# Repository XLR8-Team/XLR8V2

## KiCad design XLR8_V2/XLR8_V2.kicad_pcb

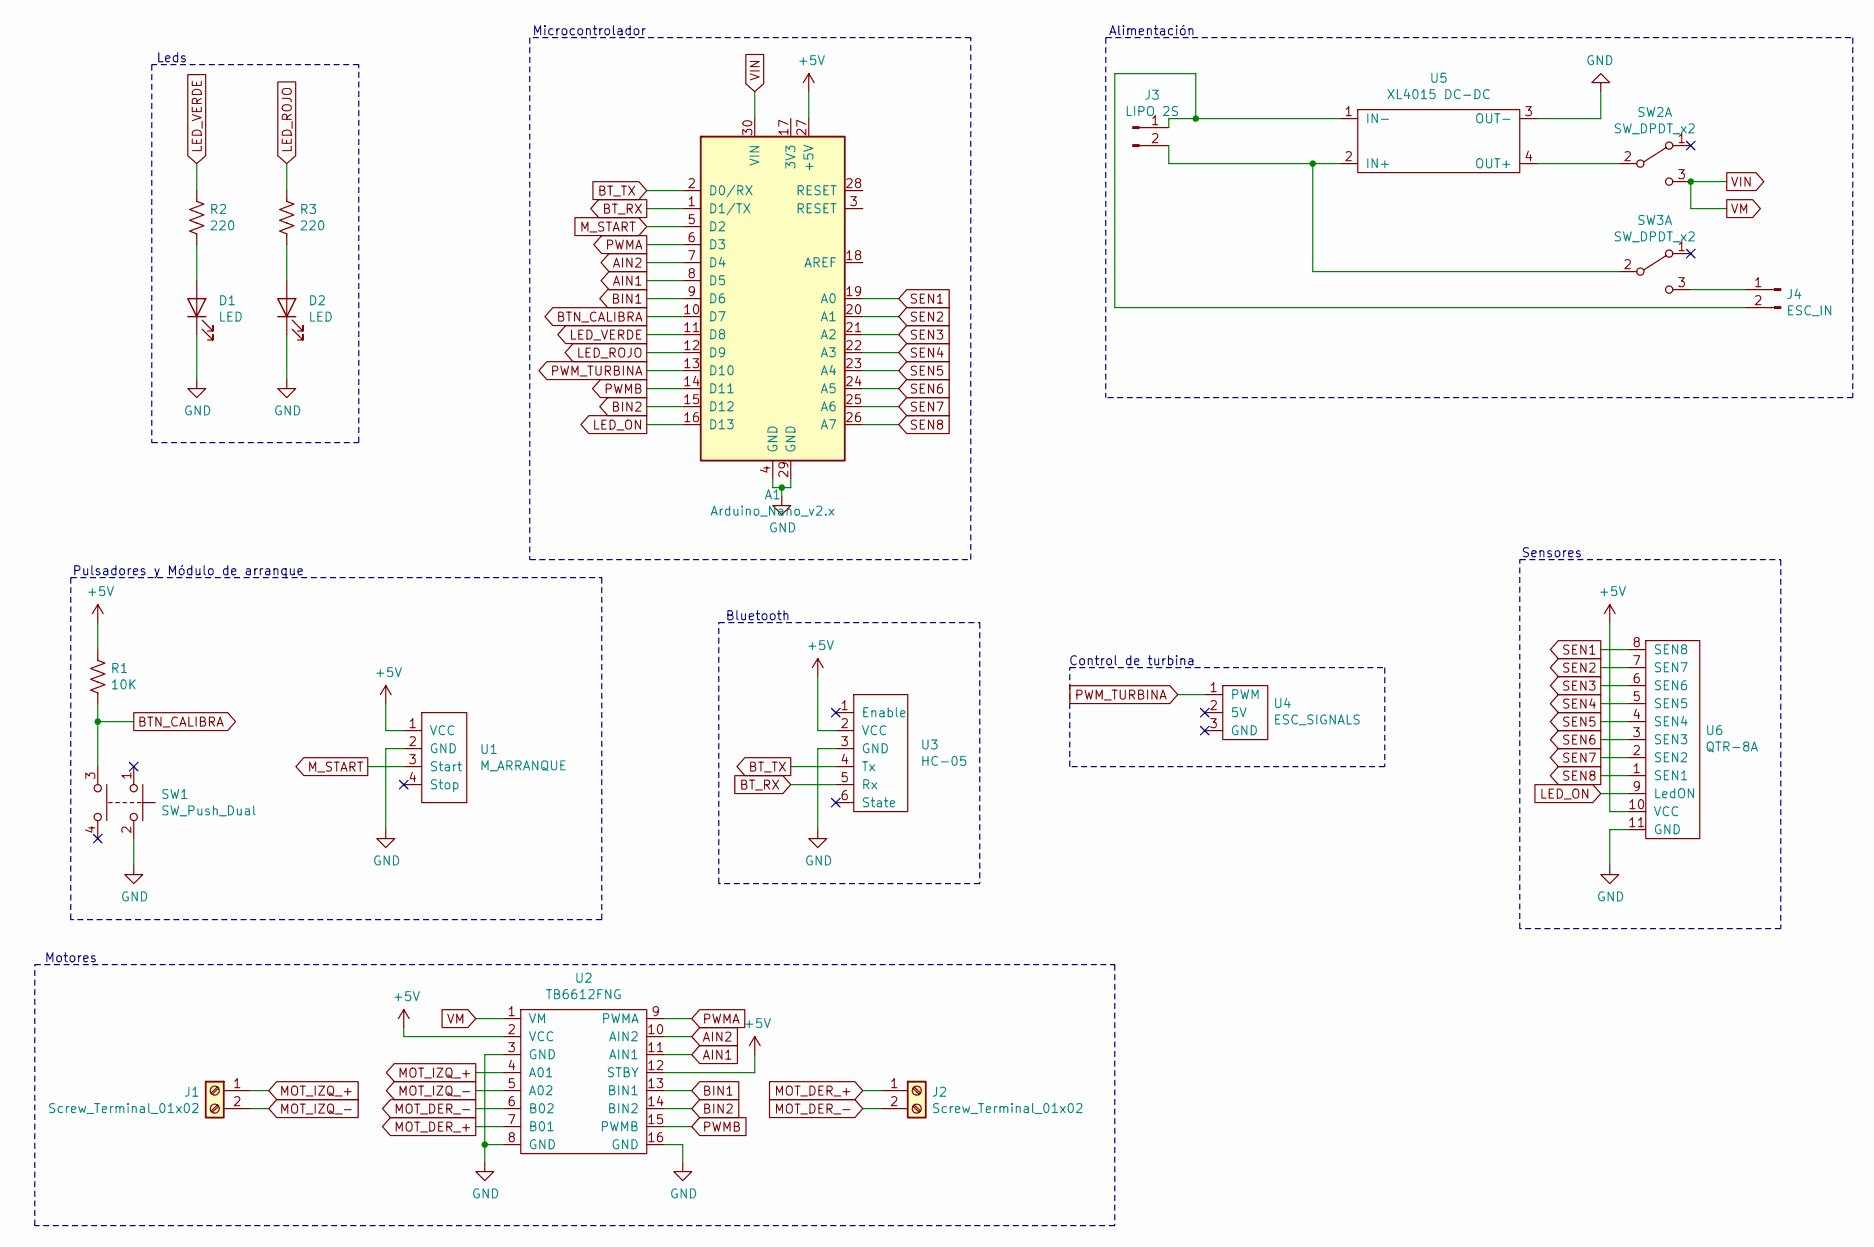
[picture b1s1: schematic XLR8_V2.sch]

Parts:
A1: Arduino_Nano_v2.x; Arduino_Nano_WithMountingHoles
D1, D2: LED; LED_D3.0mm
J1, J2: Screw_Terminal_01x02; TerminalBlock_bornier-2_P5.08mm
J3: LIPO 2S; AMASS_XT30U-M_1x02_P5.0mm_Vertical
J4: ESC_IN; PinHeader_1x02_P2.54mm_Vertical
R1: 10K; R_Axial_DIN0207_L6.3mm_D2.5mm_P7.62mm_Horizontal
R2, R3: 220; R_Axial_DIN0207_L6.3mm_D2.5mm_P7.62mm_Horizontal
SW1: SW_Push_Dual; SW_PUSH_6mm
SW2, SW3: SW_DPDT_x2; SW_CuK_OS102011MA1QN1_SPDT_Angled
U1: M_ARRANQUE; PinSocket_1x04_P2.54mm_Vertical
U2: TB6612FNG
U3: HC-05; PinSocket_1x06_P2.54mm_Vertical
U4: ESC_SIGNALS; PinHeader_1x03_P2.54mm_Vertical
U5: XL4015 DC-DC; XL4015_Converter
U6: QTR-8A; PinHeader_1x11_P2.54mm_Vertical

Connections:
+5V: A1.27 (+5V), R1.1, U1.1 (VCC), U2.2 (VCC), U2.12 (STBY), U3.2 (VCC), U6.10 (VCC)
AIN1: A1.8 (D5), U2.11 (AIN1)
AIN2: A1.7 (D4), U2.10 (AIN2)
BIN1: A1.9 (D6), U2.13 (BIN1)
BIN2: A1.15 (D12), U2.14 (BIN2)
BTN_CALIBRA: A1.10 (D7), R1.2, SW1.3
BT_RX: A1.1 (D1/TX), U3.5 (Rx)
BT_TX: A1.2 (D0/RX), U3.4 (Tx)
GND: A1.4 (GND), A1.29 (GND), D1.1 (K), D2.1 (K), SW1.2, U1.2 (GND), U2.3 (GND), U2.8 (GND), U2.16 (GND), U3.3 (GND), U5.3 (OUT-), U6.11 (GND)
LED_ON: A1.16 (D13), U6.9 (LedON)
LED_ROJO: A1.12 (D9), R3.1
LED_VERDE: A1.11 (D8), R2.1
MOT_DER_+: J2.1, U2.7 (B01)
MOT_DER_-: J2.2, U2.6 (B02)
MOT_IZQ_+: J1.1, U2.4 (A01)
MOT_IZQ_-: J1.2, U2.5 (A02)
M_START: A1.5 (D2), U1.3 (Start)
unnamed: D1.2 (A), R2.2
unnamed: D2.2 (A), R3.2
unnamed: J3.1, J4.2, U5.1 (IN-)
unnamed: J3.2, SW3.2 (B), U5.2 (IN+)
unnamed: J4.1, SW3.3 (C)
unnamed: SW2.2 (B), U5.4 (OUT+)
PWMA: A1.6 (D3), U2.9 (PWMA)
PWMB: A1.14 (D11), U2.15 (PWMB)
PWM_TURBINA: A1.13 (D10), U4.1 (PWM)
SEN1: A1.19 (A0), U6.8 (SEN8)
SEN2: A1.20 (A1), U6.7 (SEN7)
SEN3: A1.21 (A2), U6.6 (SEN6)
SEN4: A1.22 (A3), U6.5 (SEN5)
SEN5: A1.23 (A4), U6.4 (SEN4)
SEN6: A1.24 (A5), U6.3 (SEN3)
SEN7: A1.25 (A6), U6.2 (SEN2)
SEN8: A1.26 (A7), U6.1 (SEN1)
VIN: A1.30 (VIN), SW2.3 (C), U2.1 (VM)

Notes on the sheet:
Alimentación
Microcontrolador
Leds
Pulsadores y Módulo de arranque
Bluetooth
Control de turbina
Sensores
Motores

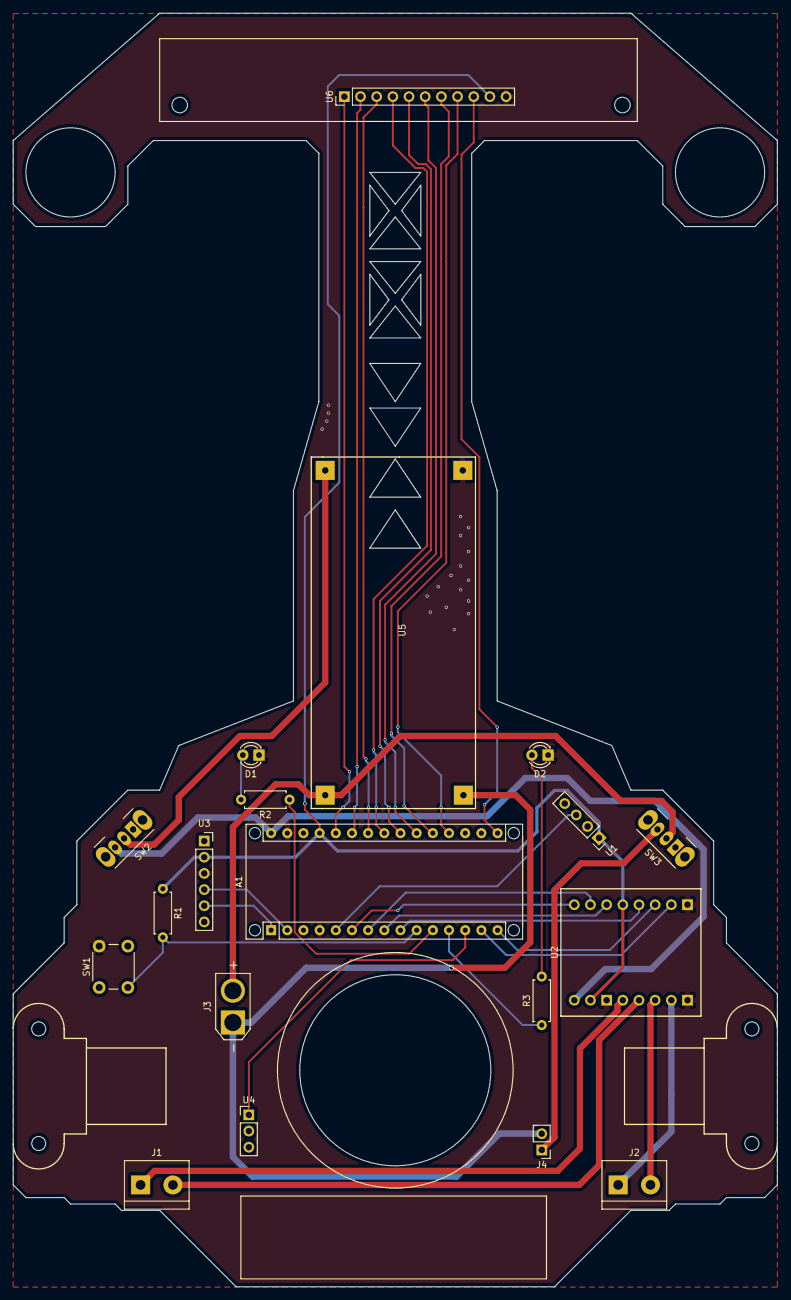
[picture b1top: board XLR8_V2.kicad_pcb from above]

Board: 2 copper layers, 120.0 x 200.0 mm, 19 parts (0 on the bottom side), 35 nets.

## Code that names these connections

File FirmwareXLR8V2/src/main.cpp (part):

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Pin Mapping:
Physical Pin      Arduino Pin    Port Pin     Function
========================================================
19                A0             PC0          SEN1
20                A1             PC1          SEN2
21                A2             PC2          SEN3
22                A3             PC3          SEN4
23                A4             PC4          SEN5
24                A5             PC5          SEN6
25                A6             PC0          SEN7
26                A7             PC1          SEN8
16                D13            PB5          LED_ON_SENSOR
13                D10            PB2          PWM_TURBINA     OC1B
05                D2             PD2          M_START         PCINT18
10                D7             PD7          BTN_CALIBRA     PCINT23
11                D8             PB0          LED_VERDE
12                D9             PB1          LED_ROJO
06                D3             PD3          PWMA            OC2B
14                D11            PB3          PWMB            OC2A
07                D4             PD4          AIN2
08                D5             PD5          AIN1
09                D6             PD6          BIN1
15                D12            PB4          BIN2
02                D0             PD0          BT_TX
01                D1             PD1          BT_RX
*/

#include <Arduino.h>
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#define MOT_IZQ_ATRAS     PD4

// Pines arranque
#define M_START         2
#define BTN_CALIBRA     7

// Setup a new OneButton on pin A1.
OneButton mStart(M_START, false);
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  DDRD |= (1 << DDD3) | (1 << DDD4) | (1 << DDD5) | (1 << DDD6); //Pin 3 del puerto D ,//Pin 4 del puerto D, Pin 5 del puerto D, Pin 6 del puerto D

  //CONFIGURACION PINES DE ENTRADA
  DDRD &= ~((1 << DDD7) | (1 << DDD2)); // Pin 7 del puerto D como entrada btn_calibra, Pin 2 del puerto D como entrada Modulo_arranque

  //CONFIGURAR PWM MOTORES
  PWM_init(); // 7812 Hz Timer 2
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  //CONFIGURAR INTERRUPCION
  PCICR |= (1 << PCIE2);
  PCMSK2 |= (1 << PCINT18); //M_START BTN_START | (1 << PCINT23
  //attachPCINT(digitalPinToPCINT(M_START), modArranque, RISING);
  //attachPCINT(digitalPinToPCINT(BTN_CALIBRA), btnChange, FALLING);
  // link the myClickFunction function to be called on a click event.
  //mStart.attachClick(modArranque);
  btnArranque.attachClick(btnChange);
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
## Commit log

2021-04-07 add pins
2021-04-08 add files pcb and reading sensors
2021-04-09 add pinout, isr, blink leds, state machine
2021-04-09 Add motor, position
2021-04-09 Add code XLR8v1
2021-04-10 add pid , frenos
2021-04-11 add b2, pwm fix
